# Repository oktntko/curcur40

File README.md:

# curcur40

**curcur40** は、[Corne Keyboard (crkbd v4)](https://github.com/foostan/crkbd) をベースに、**39キー（論理 40入力）左右分割ロープロファイル配列**、右手親指の **25 mm 光学式トラックボール**、右手人差し指内側の **アンダープレート パッシブ磁気慣性ホイール**、および **ビルトイン 11.8° テンティング（折りたたみスタンド併用で 24° / 34° 切替対応）密閉ケース** を統合したカスタムエルゴノミクスキーボードです。

> 製作・部品調達・発注手順は **[ビルドガイド (`docs/buildguide_jp.md`)](./docs/buildguide_jp.md)**、各部の設計仕様書は **[3. ドキュメントインデックス](#3-ドキュメントインデックス-documentation-index)** を参照してください。

---

## 1. 外部仕様 (External Specifications)

### 1.1 ギャラリー (Gallery)

- **[3D 組み立てアニメーション動画 (`docs/assets/assembly_animation.mp4`, 1080p 60fps)](./docs/assets/assembly_animation.mp4)**

#### 本体外観（上面・底面）

| 上面ビュー | 底面ビュー（密閉底面・折りたたみスタンド収納ポケット） |
| :---: | :---: |
|  |  |

#### ポインティング機構（25mm トラックボール ＆ アンダープレート慣性ホイール）

| 右手ホイール実装外観 | 慣性ホイールモジュール単体 |
| :---: | :---: |
|  |  |

| トラックボールカップ単体 | 25mm ボール・光学系組込 |
| :---: | :---: |
|  |  |

> 機構の動作をブラウザ上で体験できるインタラクティブ図解：
> - **[慣性ホイールの 3つのしくみ (`docs/wheel_mechanism_guide.html`)](./docs/wheel_mechanism_guide.html)**
> - **[キャリングボックスの浅角カムフタ開閉機構 (`docs/carrying_box_lid_guide.html`)](./docs/carrying_box_lid_guide.html)**

#### 基板・トッププレート外観

| 左メイン基板 表面 (`F.Cu`) | 左メイン基板 斜視 | 左メイン基板 裏面 (`B.Cu`) |
| :---: | :---: | :---: |
|  |  |  |

| 右メイン基板 表面 (`F.Cu`) | 右メイン基板 斜視 | 右メイン基板 裏面 (`B.Cu`) |
| :---: | :---: | :---: |
|  |  |  |

| 左トッププレート | 右トッププレート | TBセンサー基板 表 (`F.Cu`) | TBセンサー基板 裏 (`B.Cu`) |
| :---: | :---: | :---: | :---: |
|  |  |  |  |

#### 持ち運び用キャリングボックス（オプション）

| フタ装着時（6面フルカバー収納） | フタ取り外し・スライド挿入時 |
| :---: | :---: |
|  |  |

| ボックス本体 | 差込口断面（ゴム足フローティングレール＆TBキーパー） |
| :---: | :---: |
|  |  |

---

### 1.2 ハードウェア仕様 (Hardware Specifications)

| 項目 | 仕様 |
| :--- | :--- |
| **フォームファクタ** | 左右分割型 カラムスタッガード配列（全キー 1u・ホットスワップ対応） |
| **キー数・入力構成** | **計 40 論理スイッチ入力**（Kailh Choc V2 キースイッチ **39個** ＋ ホイール押し込み静音中クリック **1入力**）<br>・**左手 (21キー)**: メイン `3 × 5` (15) ＋ 人差し指内側縦 2キー ＋ 親指 4キー<br>・**右手 (18キー + 2ポインティング)**: メイン `3 × 5` (15) ＋ 人差し指内側下段 1キー ＋ 親指外側 2キー ＋ **慣性ホイール** ＋ **25 mm トラックボール** |
| **対応キースイッチ / キャップ** | Kailh Choc V2（`CPG1353` シリーズ）専用 ／ ロープロファイル MX 十字ステム 1u キーキャップ（`18.5 × 18.5 mm` 以下） |
| **本体外形寸法（片側）** | 幅 **`118.81 mm`** × 奥行 **`94.40 mm`** × ケース高 **`14.20 mm`（小指外端）〜 `39.02 mm`（親指内端）** |
| **テンティング角度** | ・標準（ケース単体 / スタンド収納時）: **`11.80°`** ビルトインテンティング<br>・底面埋め込み折りたたみスタンド展開時（任意）: **約 `24°`（1段目）／ 約 `34°`（2段目）** |
| **トラックボール（右手親指）** | **直径 `⌀25.0 mm` 光学式**（`800 CPI` / `1000 Hz` ポーリング、3点セラミック球支持、素手着脱可能な 3本爪スナップ保持） |
| **スクロールホイール（右手内側）** | **外径 `⌀22.0 mm × 幅 4.65 mm` 炭素鋼フライホイール**（質量 `13.20 g`、1周 **24ノッチ** 非接触磁気ラチェット［無段階強弱調整可］、長時間慣性フリースピン・指触れ即停止、静音ミドルクリック対応） |
| **接続インターフェース** | ・**PC接続**: 左右どちらでも接続可能な北面 USB Type-C（マスター自動認識）<br>・**左右間接続**: 内側側面 USB Type-C（パッシブ USB 2.0 C-to-C ケーブル使用、PC/充電器誤挿し保護付） |
| **LED ライティング** | 各キー独立 RGB バックライト（計 39灯、QMK RGB Matrix 対応） |
| **キャリングボックス（任意）** | 外寸 **`140.20 × 110.44 × 80.25 mm`**（上下リバーシブル 6面フルカバー直方体、トラックボール・折りたたみスタンド・高さ `≤ 3.0 mm` ゴム足・USB-C マグネット端子を装着したまま収納可能） |

---

### 1.3 ソフトウェア仕様 (Firmware & Keymap Specifications)

#### 基本仕様・特殊キー動作

- **対応ファームウェア**: QMK Firmware / VIA / **Vial（推奨・最大 6レイヤー、GUI リアルタイム編集対応）**
- **ポインティング ＆ スクロール専用カスタムキーコード**（Vial / VIA の `User` / `Custom` タブから任意キーへ配置可能）:

| キーコード (Vial表示) | 機能 |
| :--- | :--- |
| **`SCRL_MO` (`USER00`)** | 押している間、トラックボールが **2D 慣性高速ドラッグスクロール** に切り替わる（離すと即座にブレーキがかかり通常カーソル移動へ復帰） |
| **`SCRL_TG` (`USER01`)** | トラックボールの **2D 慣性高速ドラッグスクロール** をトグル切り替え |
| **`SCRL_SL` (`USER02`)** | 押している間、慣性を無効化した **低速精密 2D ドラッグスクロール** に切り替わる |
| **`WHL_HRZ` (`USER03`)** | 押している間、慣性ホイールの回転出力を **水平スクロール（横スクロール）** に切り替える（※`Shift` キー併用時は OS 標準の `Shift + 縦スクロール` として動作） |

- **ポインティング補助挙動**:
  - **Layer 3 自動スクロール連動**: デフォルトで **Layer 3 が有効な間も自動的に 2D 慣性ドラッグスクロールモード** になります。
  - **タッチ即停止 ＆ ズーム誤爆ガード**: 2D 慣性スクロールの惰走中にトラックボールへ軽く触れるかマウスクリックすると即座に停止します。また惰走中に `Ctrl` / `Alt` / `GUI` を押した場合も自動で慣性を停止し、意図しないブラウザ拡大縮小を防ぎます。
  - **ホイールクリック時ブランキング**: ホイール押し込み（中クリック）前後 `25 ms` の微小角度揺れをマスクし、クリックと同時の誤スクロールを抑止します。
- **ケース解体不要のブートローダ起動（DFU / `RPI-RP2` マウント）**:
  - **Bootmagic**: USB を抜いた状態で、**左手は左上端キー（`Tab` 位置 `[0, 1]`）、右手は右上端キー（`Q` 位置 `[4, 1]`）を押したまま USB を接続**。
  - キーマップ上の `QK_BOOT` キー押下でも即座に書き込みモードへ移行可能。

#### デフォルトキーマップ（Vial 標準構成：全 4レイヤー定義済）

Eucalyn 系をベースにした 40入力レイアウトに、右手内側のマウスクリック（上段＝ホイール押し込み `BTN3`、下段キー＝`BTN1`）と Tap-Hold（`Permissive Hold` ＋ `Hold On Other Key Press` 有効）を組み合わせています。

- **Layer 0（ベースレイヤー）**

| 行 | 左手 1 | 左手 2 | 左手 3 | 左手 4 | 左手 5 | 左手 内側 | 右手 内側 | 右手 5 | 右手 4 | 右手 3 | 右手 2 | 右手 1 |
| :-: | :---: | :---: | :---: | :---: | :---: | :---: | :---: | :---: | :---: | :---: | :---: | :---: |
| **上段** | `Tab` | `W` | `E` | `R` | `F` | `-` | **`BTN3` (Wheel押込)** | `J` | `U` | `I` | `O` | `Q` |
| **中段** | `A` | `S` | `D` | `T` | `G` | `Shift+;` | **`BTN1`** | `H` | `Y` | `K` | `L` | `P` |
| **下段** | `LShift` | `Z` | `X` | `C` | `V` | *(なし)* | *(TB領域)* | `B` | `N` | `M` | `,` | `.` |
| **親指** | | | `LGUI` | `Alt / 無変換` | `Ctrl / Esc` | **`LT(1, Space)`** | *(TB領域)* | *(なし)* | **`LT(2, Enter)`** | **`LT(3, 変換)`** | | |

- **Layer 1（ファンクション・括弧・ナビゲーション：`LT(1, Space)` ホールド）**
  - 左手: 上段 `F2`, `F4`, `F12`, `F11` ／ 中段 `[` (JIS `@`), `Del`, `Enter`, `Bksp`, `Macro 0` (`Win+Alt+Space`) ／ 下段・親指 `Alt + ←/↑/→/↓`
  - 右手: 各種括弧・記号類（`&`, `(`, `)`, `-`, `\`, `~`, `]`, `}`, `_`, `$`, `<`, `>`, `+`）
- **Layer 2（カーソル矢印・編集記号：`LT(2, Enter)` ホールド）**
  - 右手: 矢印キー（`I/J/K/L` 周辺に `↑` / `←` `↓` `→`）および `Bksp`, `Del`, 引用符・イコール・セミコロン類
- **Layer 3（テンキー・PageUp/Down ＋ トラックボール 2D慣性スクロール自動有効：`LT(3, 変換)` ホールド）**
  - 左手: `PageUp` / `Home`, `PageDown`, `End`、`#`
  - 右手: 3×3 テンキー（`0`〜`9`）および四則演算記号
- **Vial 初期プリセット（GUI から自由に変更・無効化可能）**:
  - **コンボ**: `BTN1` ＋ `H` 同時押し → **`BTN2`（右クリック）**
  - **Key Overrides（11種）**: JIS 環境向けのシフト記号リマップや修飾キー組み合わせ補正をプリセット収録。

---

## 2. ライセンス・謝辞 (License & Credits)

本プロジェクトは以下のオープンソースプロジェクトをベースに派生・設計されています。各オリジナル作者の皆様に深く感謝いたします。

| 対象領域 | 派生元・原著作者 | 適用ライセンス | 改変時期・主な改変内容（CC BY 4.0 Sec. 3(a) / CERN-OHL-P v2 Sec. 3.3 準拠） |
| :--- | :--- | :--- | :--- |
| **基板・プレート・ケース・ホイール・ドキュメント・スクリプト**<br>(`pcbs/`, `plates/`, `cases/`, `docs/`, `scripts/`) | **[foostan/crkbd](https://github.com/foostan/crkbd)**<br>(`foostan` / Kosuke Adachi) | **[MIT License](./LICENSE_MIT)** ＆<br>**[CC BY 4.0](./LICENSE_CC)** | `2026-10`〜`2026-11`: Corne v4 をベースに 39キー＋中クリック配列化、右手 25mm トラックボール（低プロファイル分離サブ基板）＆アンダープレート パッシブ磁気慣性ホイール（`45# Steel` ローター＋オンボード `TMAG5273`）統合、KiCad 10.0 対応、ヒートセット密閉テンティングケース・キャリングボックス新規設計 |
| **KiCad カスタムライブラリ**<br>(`pcbs/common/kbd/` 内 `kbd.*`) | **[foostan/kbd](https://github.com/foostan/kbd)**<br>(`foostan`) | **[MIT License](./pcbs/common/kbd/LICENSE)** | `2026-10`: 未使用定義の整理、KiCad 10.0 標準シンボル整合、`YS-SK6812MINI-E` Pin 2 (`DOUT`) 電気属性修正、`Kailh_Square_Silent_6.2x6.2mm` 追加、相対 3Dモデルパス化 |
| **PMW3360 シンボル・フットプリント**<br>(`pmw3360_pcb.kicad_sym`, `PMW3360DM-T2QU_16Pin.kicad_mod`) | **[siderakb/pmw3360-pcb](https://github.com/siderakb/pmw3360-pcb)**<br>(`siderakb` / `ziteh`) | **[CERN-OHL-P v2](./LICENSE_CERN_OHL_P_V2)** | `2026-10`: 未使用の `TXS0108E-QPWRQ1` シンボル削除、`PMW3360DM-T2QU` Pin 3 (`VDDPIX`) を `power_out` へ修正、KiCad 10.0 スルーホールパッド層補完、専用サブ基板 `curcur40-pmw3360` へ統合 |
| **ファームウェア (`kbd_firmware/`)**<br>(`kbd_firmware/keyboards/curcur40/`) | **[foostan/kbd_firmware](https://github.com/foostan/kbd_firmware)**<br>**[QMK](https://github.com/qmk/qmk_firmware)** / **[Vial-QMK](https://github.com/vial-kb/vial-qmk)** | **GPL-2.0-or-later** | `2026-10`〜`2026-11`: 40入力マトリクス、`I2C0` `TMAG5273`/`TLV493D-A1B6` 3Dホール慣性ホイール駆動 ＆ `SPI1` `PMW3360` 2D慣性ドラッグスクロール複合ポインティングドライバへ改変 |

---

## 3. ドキュメントインデックス (Documentation Index)

| ドキュメント | 対象読者・内容 |
| :--- | :--- |
| **[ビルドガイド (`docs/buildguide_jp.md`)](./docs/buildguide_jp.md)** | **製作・発注する方向け**: 購入パーツ一覧（BOM・URL）、JLCPCB / JLC3DP / JLCCNC の実発注手順とノウハウ、熱圧入・組立・FW書き込み手順 |
| **[ケース・プレート設計仕様書 (`docs/case_spec.md`)](./docs/case_spec.md)** | **内部設計**: 垂直 Z軸スタックアップ、全 19箇所インサート座標、トッププレート、ボトムケース・スタンドポケット・USB-C 受け棚の設計根拠 |
| **[PCB・回路設計仕様書 (`docs/pcb_spec.md`)](./docs/pcb_spec.md)** | **内部設計**: 全3基板＋3-in-1 パネル仕様、電源/ESD/左右判定/センサー回路の設計根拠、RP2040 ピンアサイン、SMD 部品（LCSC）一覧 |
| **[トラックボール設計仕様書 (`docs/trackball_spec.md`)](./docs/trackball_spec.md)** | **内部設計**: PMW3360 + LM19 光学距離（`2.40 mm`）設計、55° セラミック支持球の乗り上げ防止力学、2D慣性ドラッグスクロール FW 処理 |
| **[慣性ホイール設計仕様書 (`docs/wheel_spec.md`)](./docs/wheel_spec.md)** | **内部設計**: `⌀2.00 H7` 中心貫通穴 `45# Steel` フライホイール、平行ピン＆シム内輪支持、Cクリップシーソー機構、無段階磁気デテント、オンボード 3Dホール角度復調 FW 処理 |
| **[キャリングボックス設計仕様書 (`docs/carrying_box_spec.md`)](./docs/carrying_box_spec.md)** | **内部設計**: 互い違いウェッジ相殺配置、ゴム足フローティングレール、長スパン浅角カム式スナップフタの力学設計 |
| **[体験型 HTML 図解: 慣性ホイール (`docs/wheel_mechanism_guide.html`)](./docs/wheel_mechanism_guide.html)** | ブラウザで動かせる慣性スピン・磁気ノッチ調整・シーソークリックのインタラクティブ解説 |
| **[体験型 HTML 図解: スナップフタ (`docs/carrying_box_lid_guide.html`)](./docs/carrying_box_lid_guide.html)** | ブラウザで動かせるキャリングボックス浅角カムスナップフタの開閉力学解説 |
| **[スクリプト・自動検証リファレンス (`scripts/README.md`)](./scripts/README.md)** | **開発・検証向け**: 3D CAD・プレート・JLCPCB データ・プレビュー生成スクリプト（全 12本）の実行方法と DFM / 6-DOF / 干渉ゼロ検証基準 |
| **[ファームウェア README (`kbd_firmware/readme.md`)](./kbd_firmware/readme.md)** | QMK / Vial ビルドコマンドおよびカスタムキーコード概要（英語） |

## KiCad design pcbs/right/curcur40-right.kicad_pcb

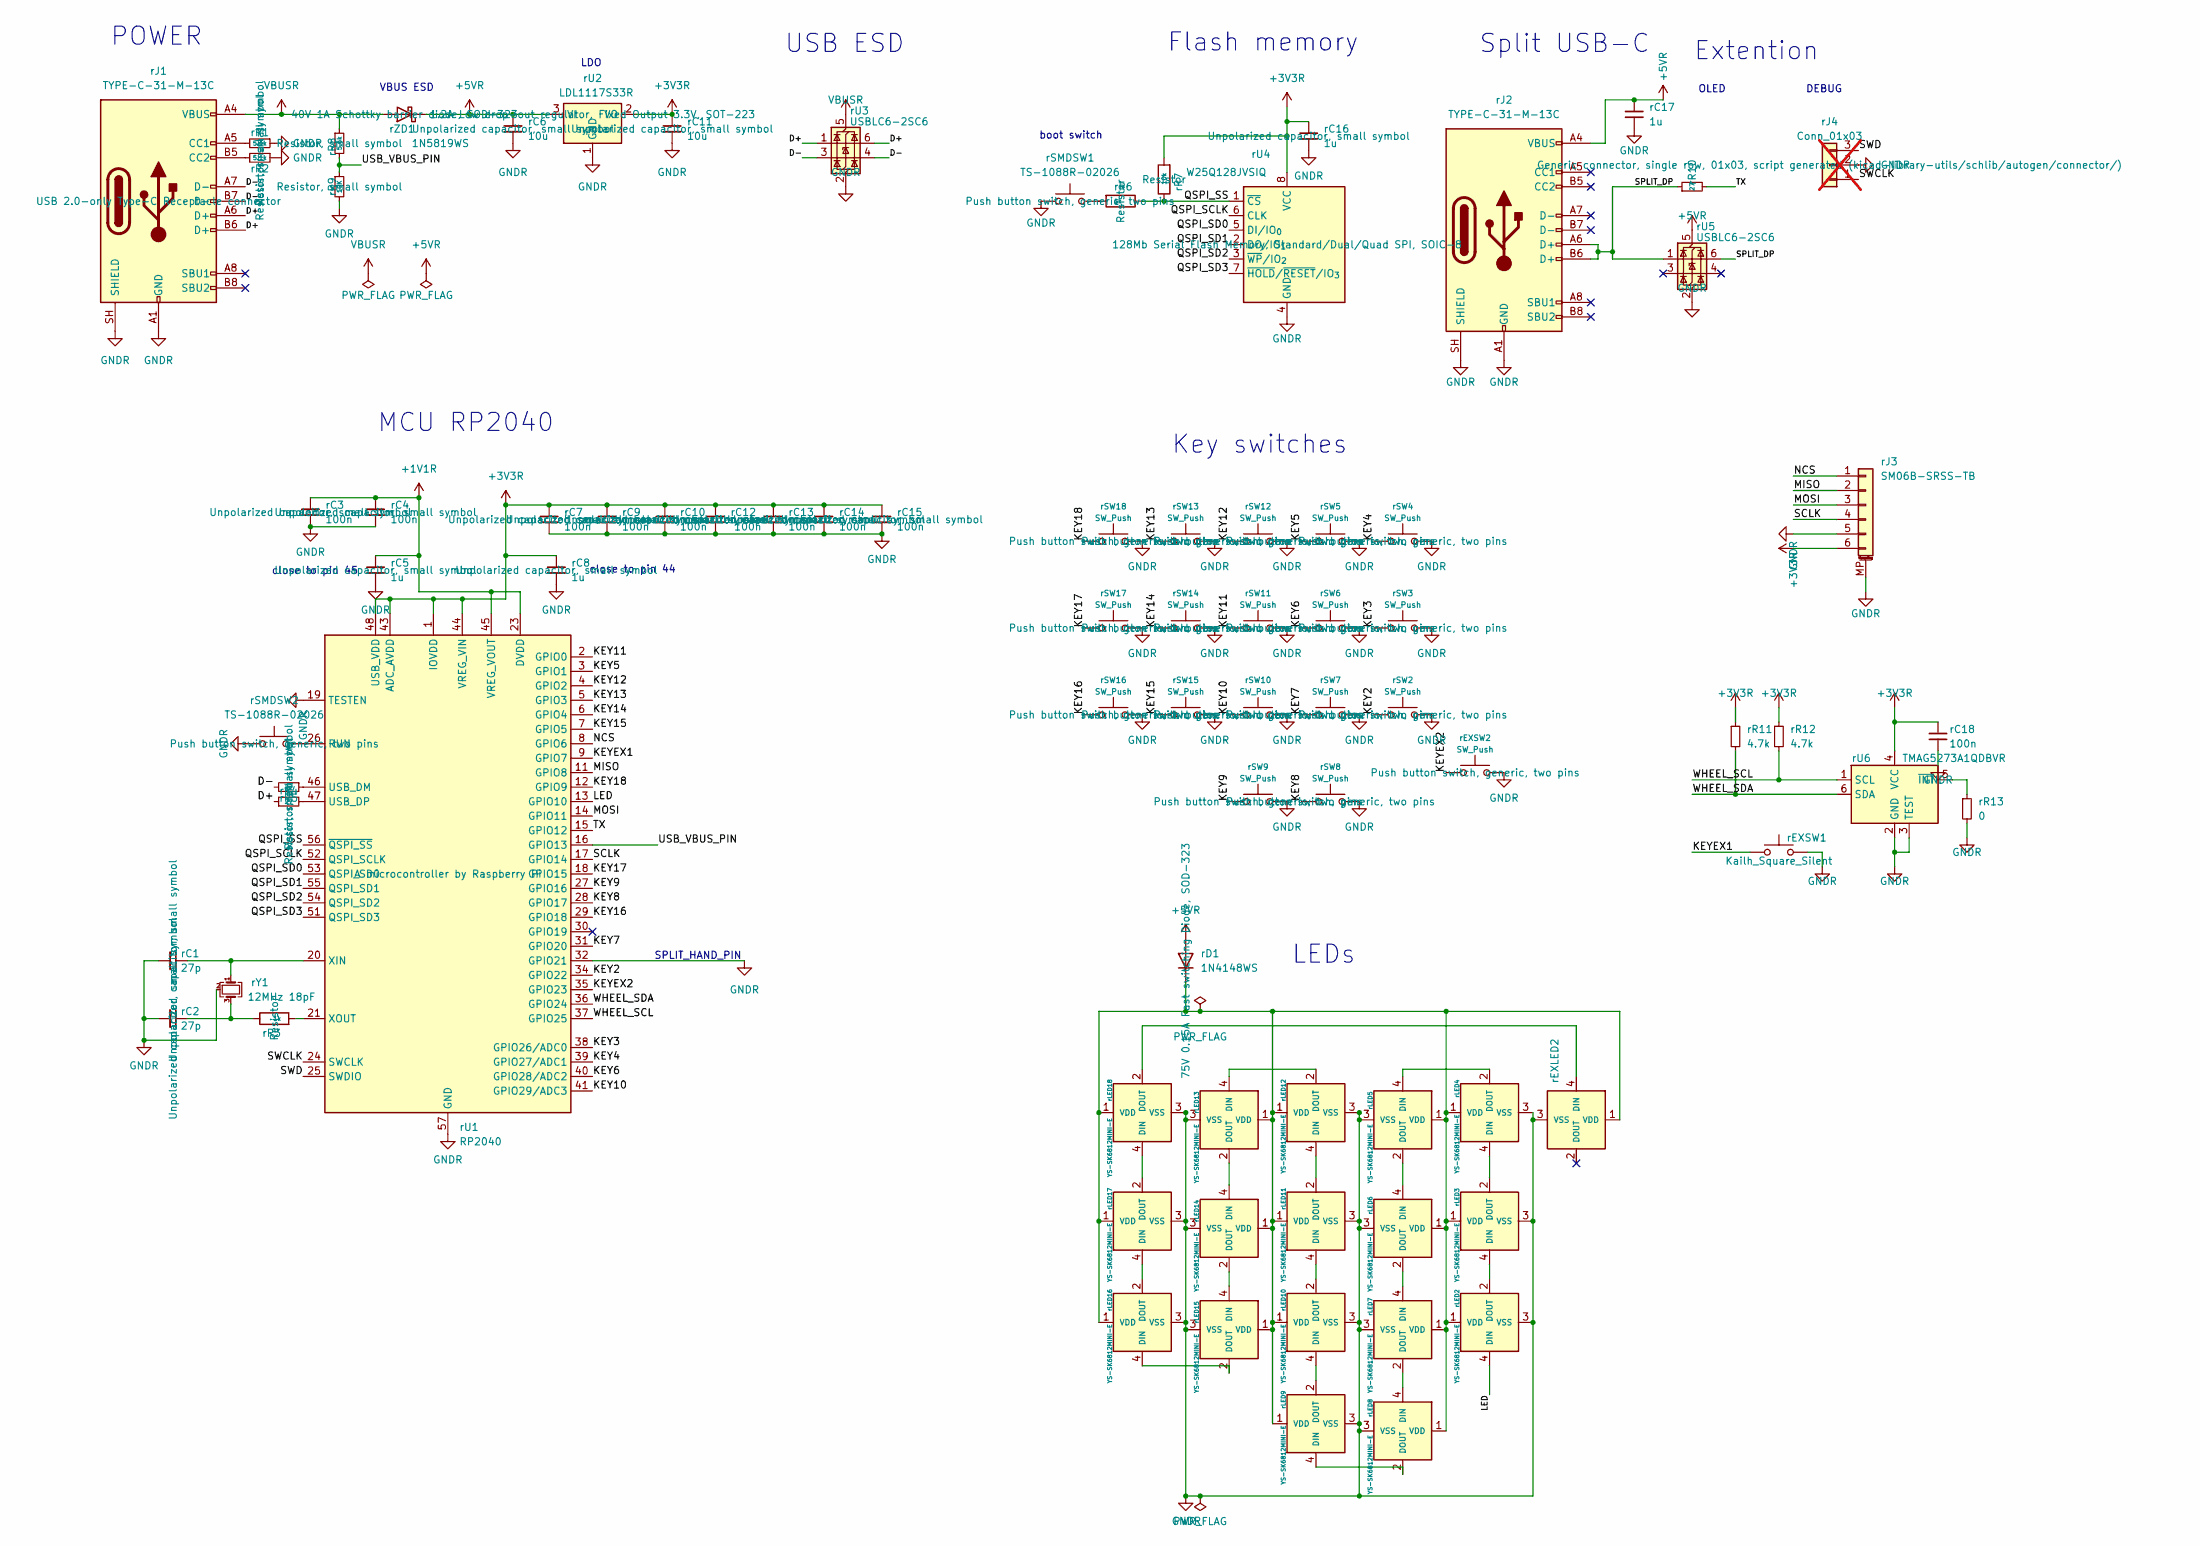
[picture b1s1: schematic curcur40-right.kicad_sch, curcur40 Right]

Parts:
rC1, rC2: 27p; C_0402_1005Metric
rC3, rC4, rC7, rC9, rC10, rC12, rC13, rC14, rC15: 100n; C_0402_1005Metric
rC5, rC8, rC16: 1u; C_0402_1005Metric
rC6, rC11: 10u; C_0402_1005Metric
rC17: 1u; C_0402_1005Metric; JLCPCB Part # C52923
rC18: 100n; C_0402_1005Metric; JLCPCB Part # C1525
rD1: 1N4148WS; D_SOD-323; JLCPCB Part # C2128
rEXLED2: YS-SK6812MINI-E
rEXSW1: Kailh_Square_Silent; Kailh_Square_Silent_6.2x6.2mm
rEXSW2: SW_Push; keyswitch_choc12_hotswap_1u
rJ1, rJ2: TYPE-C-31-M-13C; USB_C_Receptacle_TYPE-C-31-M-13C; JLCPCB Part # C2848620
rJ3: SM06B-SRSS-TB; JST_SH_SM06B-SRSS-TB_1x06-1MP_P1.00mm_Horizontal; LCSC C160405
rJ4: Conn_01x03; PinHeader_1x03_P2.54mm_Vertical; not fitted
rLED2, rLED3, rLED4, rLED5, rLED6, rLED7, rLED8, rLED9, rLED10, rLED11, rLED12, rLED13, rLED14, rLED15, rLED16, rLED17, rLED18: YS-SK6812MINI-E
rR1, rR2: 5.1k; R_0402_1005Metric
rR3, rR6: 1k; R_0402_1005Metric
rR4, rR5: 27; R_0402_1005Metric
rR7: 10k; R_0402_1005Metric
rR8: 5.6k; R_0402_1005Metric
rR9: 10K; R_0402_1005Metric
rR10: 27; R_0402_1005Metric; JLCPCB Part # C2909343
rR11, rR12: 4.7k; R_0402_1005Metric
rR13: 0; R_0402_1005Metric; LCSC C17168
rSMDSW1, rSMDSW2: TS-1088R-02026; JLCPCB Part # C455280
rSW2, rSW3, rSW4, rSW5, rSW6, rSW7, rSW8, rSW9, rSW10, rSW11, rSW12, rSW13, rSW14, rSW15, rSW16, rSW17, rSW18: SW_Push; keyswitch_choc12_hotswap_1u
rU1: RP2040; QFN-56-1EP_7x7mm_P0.4mm_EP3.2x3.2mm; JLCPCB Part # C2040
rU2: LDL1117S33R; SOT-223-3_TabPin2; JLCPCB Part # C435835
rU3, rU5: USBLC6-2SC6; SOT-23-6; JLCPCB Part # C7519
rU4: W25Q128JVSIQ; SOIC-8_5.3x5.3mm_P1.27mm; JLCPCB Part # C113767
rU6: TMAG5273A1QDBVR; SOT-23-6; LCSC C3716049
rY1: 12MHz 18pF; Crystal_SMD_3225-4Pin_3.2x2.5mm; MFR.Part # Q22FA23V0041800; JLCPCB Part # C91749
rZD1: 1N5819WS; D_SOD-323; JLCPCB Part # C191023

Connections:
+1V1R: rC3.1, rC4.1, rC5.1, rU1.23 (DVDD), rU1.45 (VREG_VOUT), rU1.50 (DVDD)
+3V3R: rC7.1, rC8.1, rC9.1, rC10.1, rC11.1, rC12.1, rC13.1, rC14.1, rC15.1, rC16.1, rC18.1, rJ3.6, rR7.2, rR11.1, rR12.1, rU1.1 (IOVDD), rU1.10 (IOVDD), rU1.22 (IOVDD), rU1.33 (IOVDD), rU1.42 (IOVDD), rU1.43 (ADC_AVDD), rU1.44 (VREG_VIN), rU1.48 (USB_VDD), rU1.49 (IOVDD), rU2.2 (VO), rU4.8 (VCC), rU6.4 (VCC)
+5VR: rC6.1, rC17.1, rD1.2 (A), rJ2.A4 (VBUS), rJ2.A9 (VBUS), rJ2.B4 (VBUS), rJ2.B9 (VBUS), rU2.3 (VI), rU5.5 (VBUS), rZD1.1 (K)
/D+: rJ1.A6 (D+), rJ1.B6 (D+), rR4.1, rU3.1 (I/O1), rU3.6 (I/O1)
/D-: rJ1.A7 (D-), rJ1.B7 (D-), rR5.2, rU3.3 (I/O2), rU3.4 (I/O2)
/KEY2: rSW2.1, rU1.34 (GPIO22)
/KEY3: rSW3.1, rU1.38 (GPIO26/ADC0)
/KEY4: rSW4.1, rU1.39 (GPIO27/ADC1)
/KEY5: rSW5.1, rU1.3 (GPIO1)
/KEY6: rSW6.1, rU1.40 (GPIO28/ADC2)
/KEY7: rSW7.1, rU1.31 (GPIO20)
/KEY8: rSW8.1, rU1.28 (GPIO17)
/KEY9: rSW9.1, rU1.27 (GPIO16)
/KEY10: rSW10.1, rU1.41 (GPIO29/ADC3)
/KEY11: rSW11.1, rU1.2 (GPIO0)
/KEY12: rSW12.1, rU1.4 (GPIO2)
/KEY13: rSW13.1, rU1.5 (GPIO3)
/KEY14: rSW14.1, rU1.6 (GPIO4)
/KEY15: rSW15.1, rU1.7 (GPIO5)
/KEY16: rSW16.1, rU1.29 (GPIO18)
/KEY17: rSW17.1, rU1.18 (GPIO15)
/KEY18: rSW18.1, rU1.12 (GPIO9)
/KEYEX1: rEXSW1.1, rU1.9 (GPIO7)
/KEYEX2: rEXSW2.1, rU1.35 (GPIO23)
/LED: rLED2.4 (DIN), rU1.13 (GPIO10)
/MISO: rJ3.2, rU1.11 (GPIO8)
/MOSI: rJ3.3, rU1.14 (GPIO11)
/NCS: rJ3.1, rU1.8 (GPIO6)
/QSPI_SCLK: rU1.52 (QSPI_SCLK), rU4.6 (CLK)
/QSPI_SD0: rU1.53 (QSPI_SD0), rU4.5 (DI/IO_{0})
/QSPI_SD1: rU1.55 (QSPI_SD1), rU4.2 (DO/IO_{1})
/QSPI_SD2: rU1.54 (QSPI_SD2), rU4.3 (~WP/IO_{2})
/QSPI_SD3: rU1.51 (QSPI_SD3), rU4.7 (~HOLD/~RESET/IO_{3})
/QSPI_SS: rR6.1, rR7.1, rU1.56 (~QSPI_SS), rU4.1 (~CS)
/SCLK: rJ3.4, rU1.17 (GPIO14)
/SPLIT_DP: rJ2.A6 (D+), rJ2.B6 (D+), rR10.1, rU5.1 (I/O1), rU5.6 (I/O1)
/SWCLK: rJ4.1, rU1.24 (SWCLK)
/SWD: rJ4.3, rU1.25 (SWDIO)
/TX: rR10.2, rU1.15 (GPIO12)
/USB_VBUS_PIN: rR8.2, rR9.1, rU1.16 (GPIO13)
/WHEEL_SCL: rR12.2, rU1.37 (GPIO25), rU6.1 (SCL)
/WHEEL_SDA: rR11.2, rU1.36 (GPIO24), rU6.6 (SDA)
GNDR: rC1.2, rC2.2, rC3.2, rC4.2, rC5.2, rC6.2, rC7.2, rC8.2, rC9.2, rC10.2, rC11.2, rC12.2, rC13.2, rC14.2, rC15.2, rC16.2, rC17.2, rC18.2, rEXLED2.3 (VSS), rEXSW1.2, rEXSW2.2, rJ1.A1 (GND), rJ1.A12 (GND), rJ1.B1 (GND), rJ1.B12 (GND), rJ1.SH (SHIELD), rJ2.A1 (GND), rJ2.A12 (GND), rJ2.B1 (GND), rJ2.B12 (GND), rJ2.SH (SHIELD), rJ3.5, rJ3.MP (MountPin), rJ4.2, rLED2.3 (VSS), rLED3.3 (VSS), rLED4.3 (VSS), rLED5.3 (VSS), rLED6.3 (VSS), rLED7.3 (VSS), rLED8.3 (VSS), rLED9.3 (VSS), rLED10.3 (VSS), rLED11.3 (VSS), rLED12.3 (VSS), rLED13.3 (VSS), rLED14.3 (VSS), rLED15.3 (VSS), rLED16.3 (VSS), rLED17.3 (VSS), rLED18.3 (VSS), rR1.1, rR2.1, rR9.2, rR13.2, rSMDSW1.1, rSMDSW2.1, rSW2.2, rSW3.2, rSW4.2, rSW5.2, rSW6.2, rSW7.2, rSW8.2, rSW9.2, rSW10.2, rSW11.2, rSW12.2, rSW13.2, rSW14.2, rSW15.2, rSW16.2, rSW17.2, rSW18.2, rU1.19 (TESTEN), rU1.32 (GPIO21), rU1.57 (GND), rU2.1 (GND), rU3.2 (GND), rU4.4 (GND), rU5.2 (GND), rU6.2 (GND), rU6.3 (TEST), rY1.2 (G), rY1.4 (G)
unnamed: rC2.1, rR3.1, rY1.3
unnamed: rD1.1 (K), rEXLED2.1 (VDD), rLED2.1 (VDD), rLED3.1 (VDD), rLED4.1 (VDD), rLED5.1 (VDD), rLED6.1 (VDD), rLED7.1 (VDD), rLED8.1 (VDD), rLED9.1 (VDD), rLED10.1 (VDD), rLED11.1 (VDD), rLED12.1 (VDD), rLED13.1 (VDD), rLED14.1 (VDD), rLED15.1 (VDD), rLED16.1 (VDD), rLED17.1 (VDD), rLED18.1 (VDD)
unnamed: rEXLED2.4 (DIN), rLED18.2 (DOUT)
unnamed: rJ1.A5 (CC1), rR1.2
unnamed: rJ1.B5 (CC2), rR2.2
unnamed: rLED2.2 (DOUT), rLED3.4 (DIN)
unnamed: rLED3.2 (DOUT), rLED4.4 (DIN)
unnamed: rLED4.2 (DOUT), rLED5.4 (DIN)
unnamed: rLED5.2 (DOUT), rLED6.4 (DIN)
unnamed: rLED6.2 (DOUT), rLED7.4 (DIN)
unnamed: rLED7.2 (DOUT), rLED8.4 (DIN)
unnamed: rLED8.2 (DOUT), rLED9.4 (DIN)
unnamed: rLED9.2 (DOUT), rLED10.4 (DIN)
unnamed: rLED10.2 (DOUT), rLED11.4 (DIN)
unnamed: rLED11.2 (DOUT), rLED12.4 (DIN)
unnamed: rLED12.2 (DOUT), rLED13.4 (DIN)
unnamed: rLED13.2 (DOUT), rLED14.4 (DIN)
unnamed: rLED14.2 (DOUT), rLED15.4 (DIN)
unnamed: rLED15.2 (DOUT), rLED16.4 (DIN)
unnamed: rLED16.2 (DOUT), rLED17.4 (DIN)
unnamed: rLED17.2 (DOUT), rLED18.4 (DIN)
unnamed: rR6.2, rSMDSW1.2
unnamed: rSMDSW2.2, rU1.26 (RUN)
unnamed: rR5.1, rU1.46 (USB_DM)
unnamed: rR4.2, rU1.47 (USB_DP)
unnamed: rC1.1, rU1.20 (XIN), rY1.1
unnamed: rR3.2, rU1.21 (XOUT)
unnamed: rR13.1, rU6.5 (~INT)
VBUSR: rJ1.A4 (VBUS), rJ1.A9 (VBUS), rJ1.B4 (VBUS), rJ1.B9 (VBUS), rR8.1, rU3.5 (VBUS), rZD1.2 (A)

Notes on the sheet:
USB ESD
Split USB-C
Flash memory
MCU RP2040
DEBUG
POWER
boot switch
LDO
Key switches
LEDs
Extention
VBUS ESD
OLED
close to pin 45
close to pin 44
SPLIT_HAND_PIN

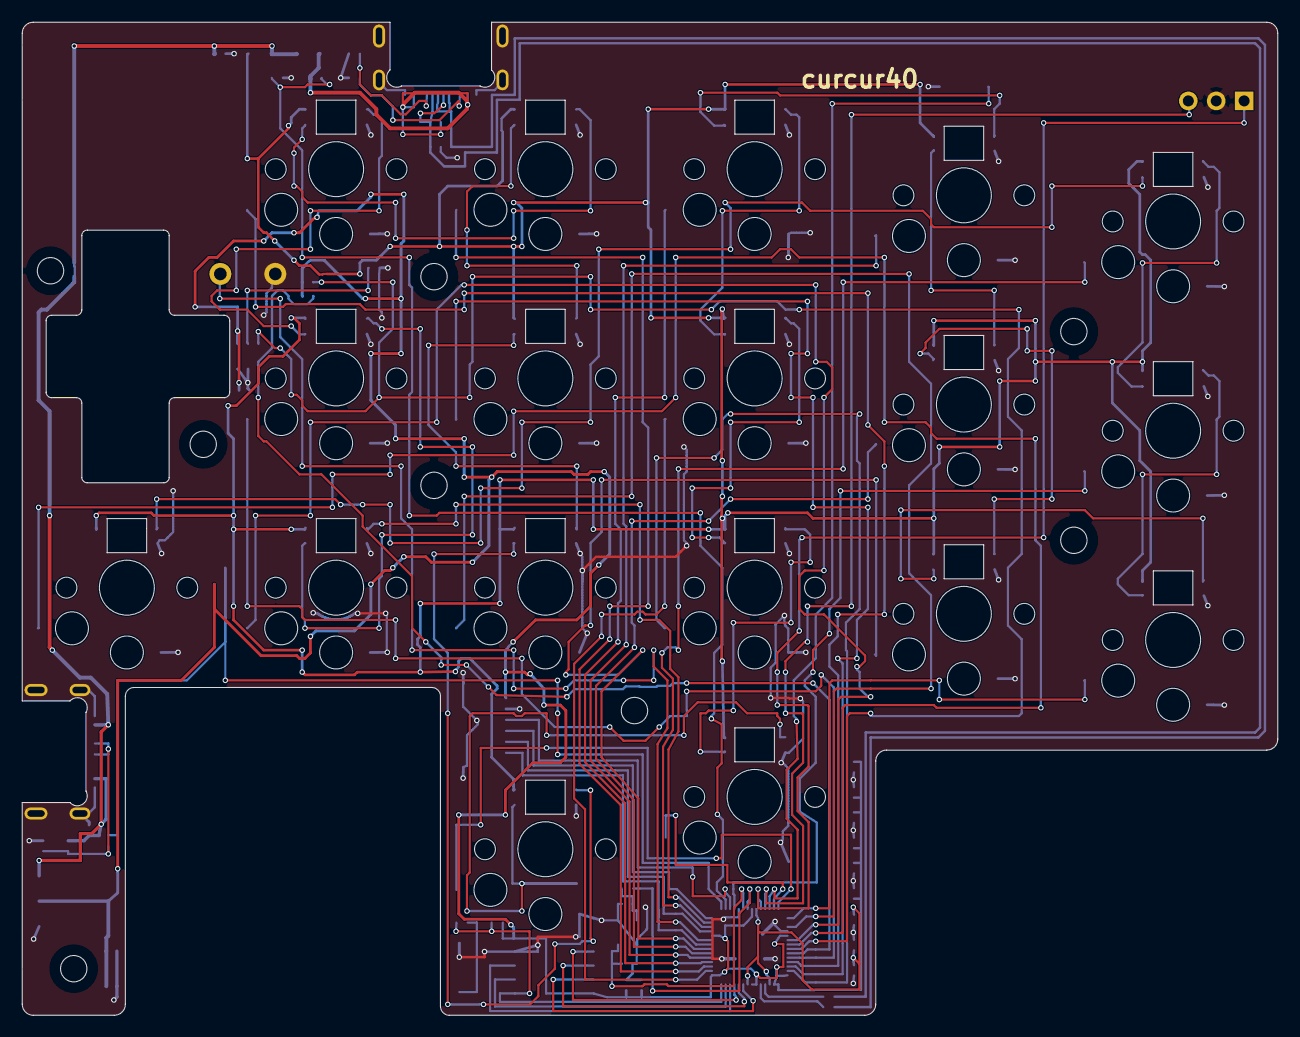
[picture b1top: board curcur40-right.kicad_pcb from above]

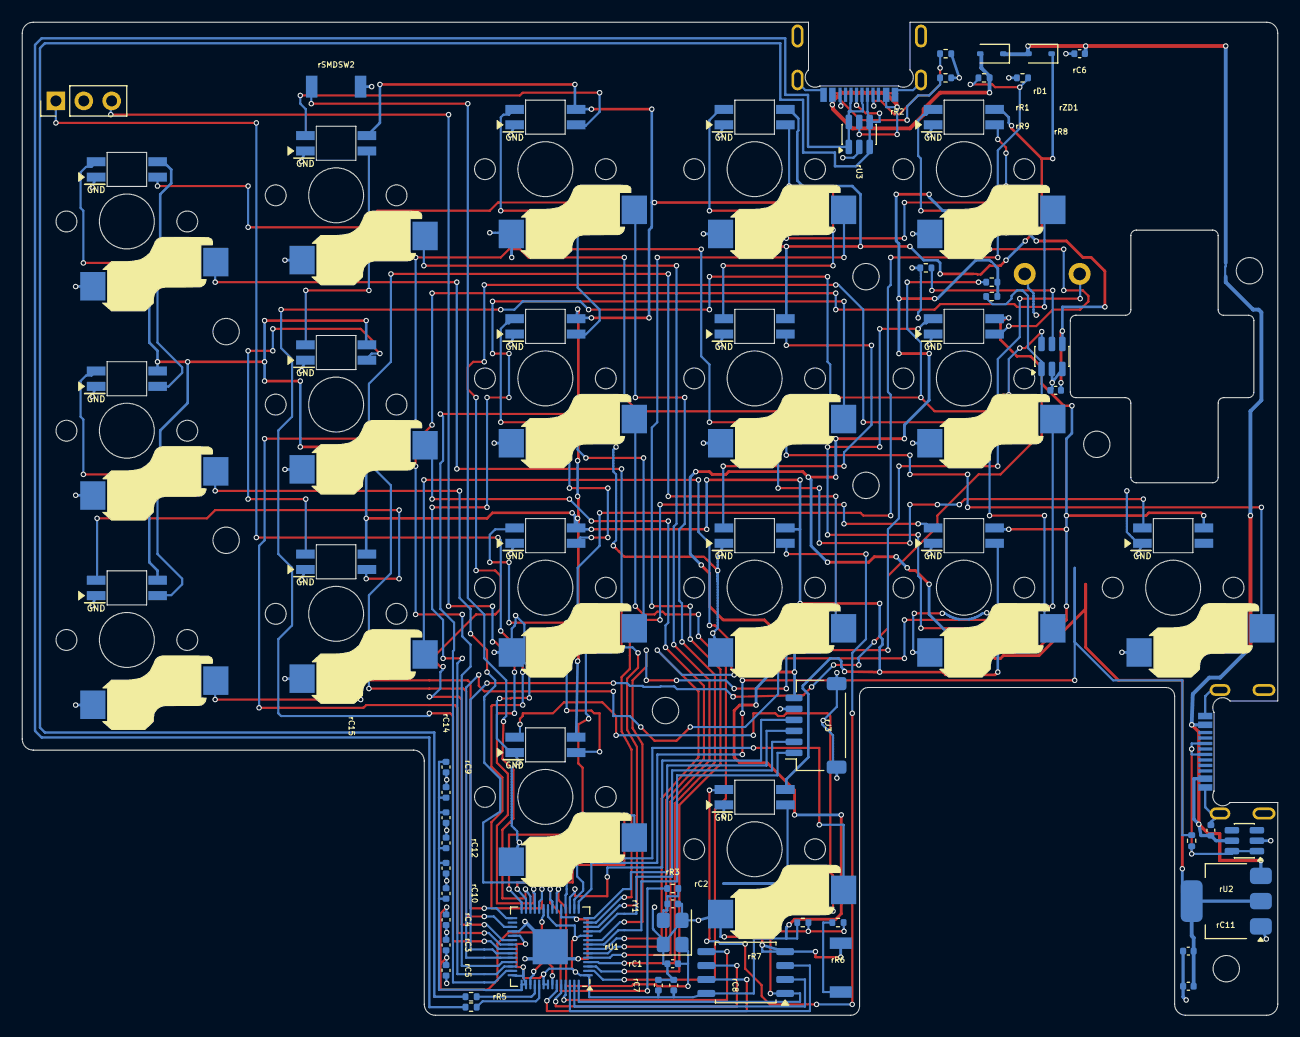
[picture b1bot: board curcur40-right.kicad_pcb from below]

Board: 2 copper layers, 114.3 x 90.4 mm, 83 parts (83 on the bottom side), 72 nets.

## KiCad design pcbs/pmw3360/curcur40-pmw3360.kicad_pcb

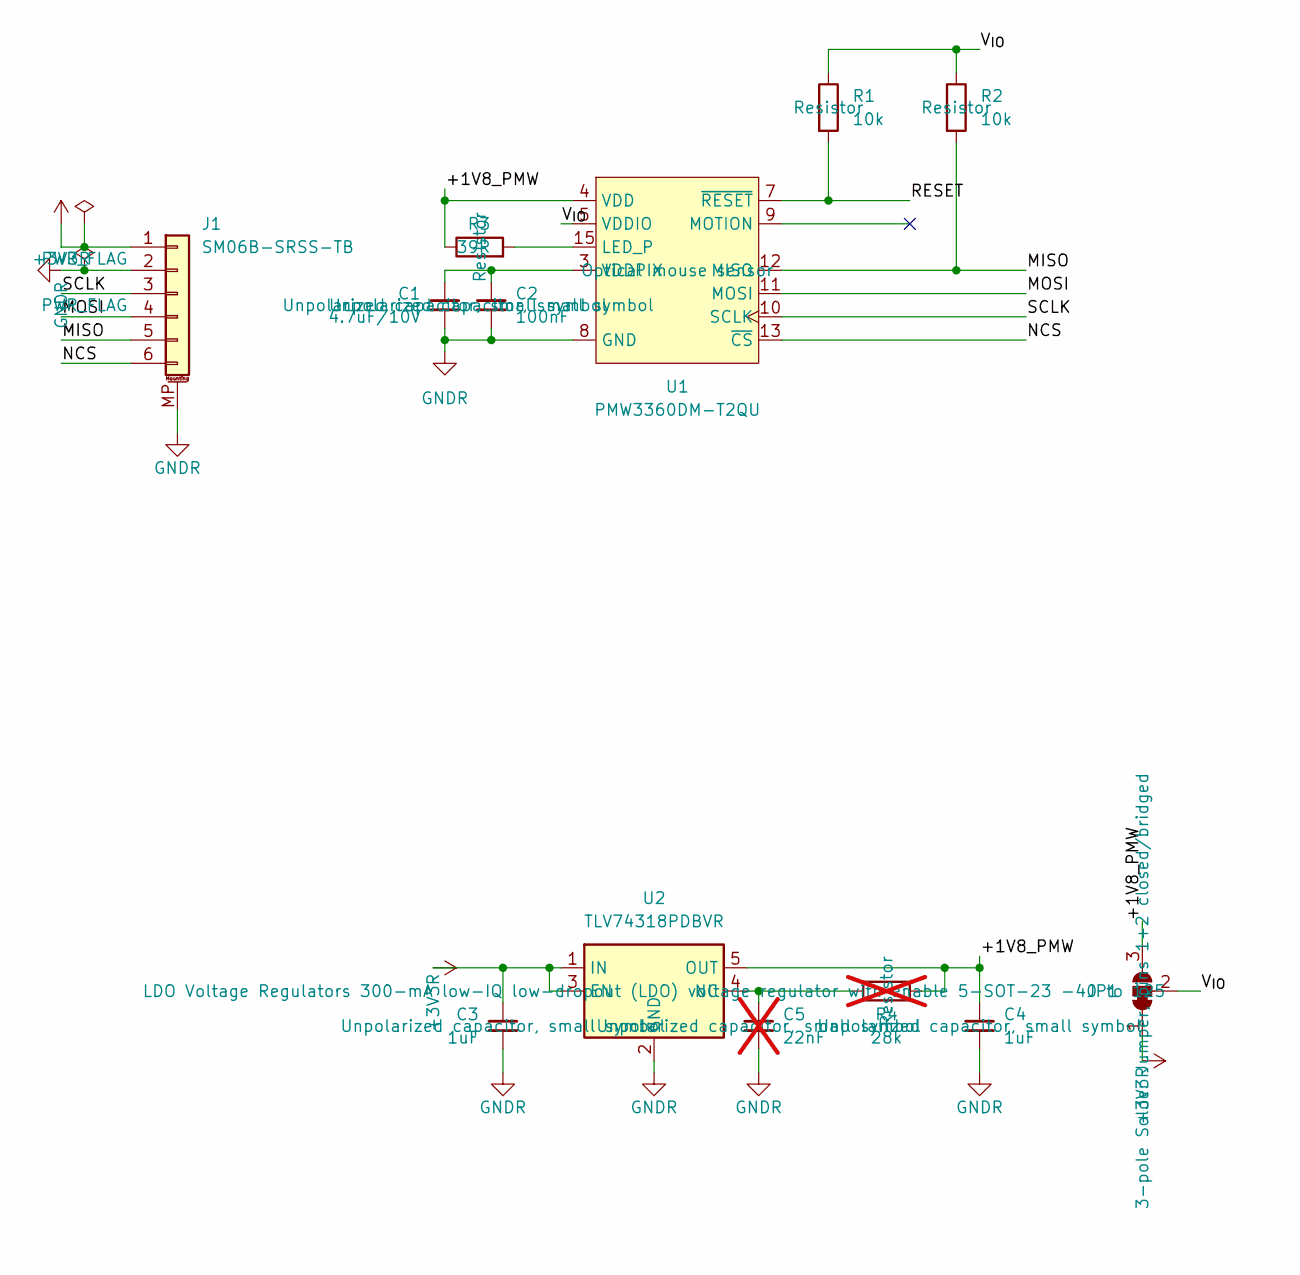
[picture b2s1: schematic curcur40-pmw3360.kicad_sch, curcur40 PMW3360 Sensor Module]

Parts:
C1: 4.7uF/10V; C_0603_1608Metric_Pad1.08x0.95mm_HandSolder; Mfr. # CL10A475KO8NNNC; LCSC C19666
C2: 100nF; C_0603_1608Metric_Pad1.08x0.95mm_HandSolder; Mfr. # CC0603KRX7R9BB104; LCSC C14663
C3, C4: 1uF; C_0603_1608Metric_Pad1.08x0.95mm_HandSolder; Mfr. # CL10A105KB8NNNC; LCSC C15849
C5: 22nF; C_0603_1608Metric_Pad1.08x0.95mm_HandSolder; Mfr. # CL10B223KB8NNNC; LCSC C21122; not fitted
J1: SM06B-SRSS-TB; JST_SH_SM06B-SRSS-TB_1x06-1MP_P1.00mm_Horizontal; LCSC C160405
JP1: SolderJumper_3_Bridged12; SolderJumper-3_P1.3mm_Bridged12_RoundedPad1.0x1.5mm_NumberL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
R1, R2: 10k; R_0603_1608Metric_Pad0.98x0.95mm_HandSolder; Mfr. # 0603WAF1002T5E; LCSC C25804
R3: 39R; R_0603_1608Metric_Pad0.98x0.95mm_HandSolder; Mfr. # 0603WAF390JT5E; LCSC C23154
R4: 28k; R_0603_1608Metric_Pad0.98x0.95mm_HandSolder; not fitted
U1: PMW3360DM-T2QU; PMW3360DM-T2QU_16Pin
U2: TLV74318PDBVR; SOT-23-5; Mfr. # TLV74318PDBVR; LCSC C485152

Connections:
+3V3R: C3.1, J1.1, JP1.1 (A), U2.1 (IN), U2.3 (EN)
/+1V8_PMW: C4.1, JP1.3 (B), R3.1, R4.1, U1.4 (VDD), U2.5 (OUT)
/MISO: J1.5, R2.2, U1.12 (MISO)
/MOSI: J1.4, U1.11 (MOSI)
/NCS: J1.6, U1.13 (~CS)
/RESET: R1.2, U1.7 (~RESET)
/SCLK: J1.3, U1.10 (SCLK)
/V_{IO}: JP1.2 (C), R1.1, R2.1, U1.5 (VDDIO)
GNDR: C1.2, C2.2, C3.2, C4.2, C5.2, J1.2, J1.MP (MountPin), U1.8 (GND), U2.2 (GND)
unnamed: R3.2, U1.15 (LED_P)
unnamed: C1.1, C2.1, U1.3 (VDDPIX)
unnamed: C5.1, R4.2, U2.4 (NC)

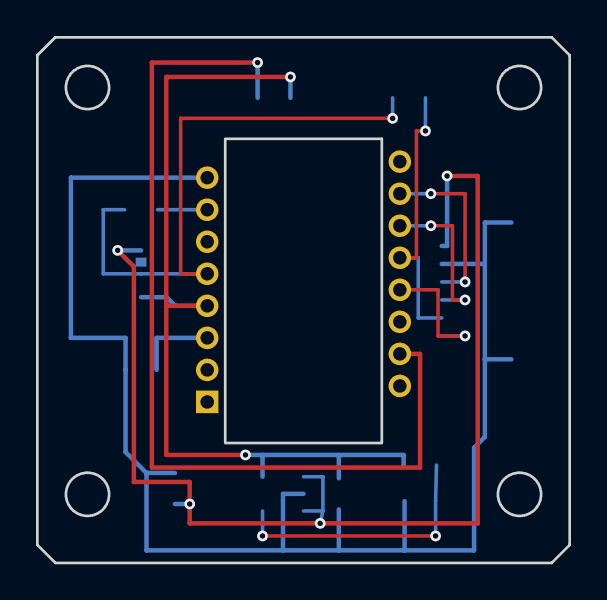
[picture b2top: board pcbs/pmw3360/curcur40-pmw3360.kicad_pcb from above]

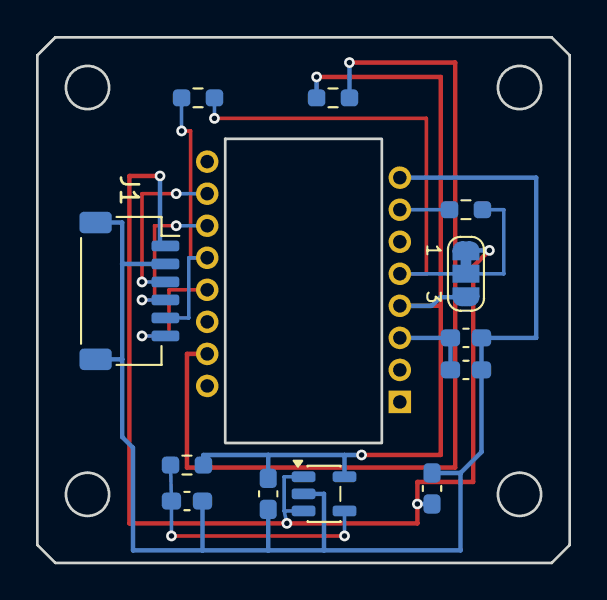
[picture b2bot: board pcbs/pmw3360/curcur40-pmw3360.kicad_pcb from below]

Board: 2 copper layers, 29.6 x 29.2 mm, 13 parts (13 on the bottom side), 12 nets.

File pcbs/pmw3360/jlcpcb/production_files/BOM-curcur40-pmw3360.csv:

Comment,Designator,Footprint,LCSC
100nF,C2,C_0603_1608Metric,C14663
1uF,"C3,C4",C_0603_1608Metric,C15849
SM06B-SRSS-TB(LF)(SN),J1,JST_SH_SM06B-SRSS-TB_1x06-1MP_P1.00mm_Horizontal,C160405
4.7uF/10V,C1,C_0603_1608Metric,C19666
39R,R3,R_0603_1608Metric,C23154
10k,"R1,R2",R_0603_1608Metric,C25804
TLV74318PDBVR,U2,SOT-23-5,C485152

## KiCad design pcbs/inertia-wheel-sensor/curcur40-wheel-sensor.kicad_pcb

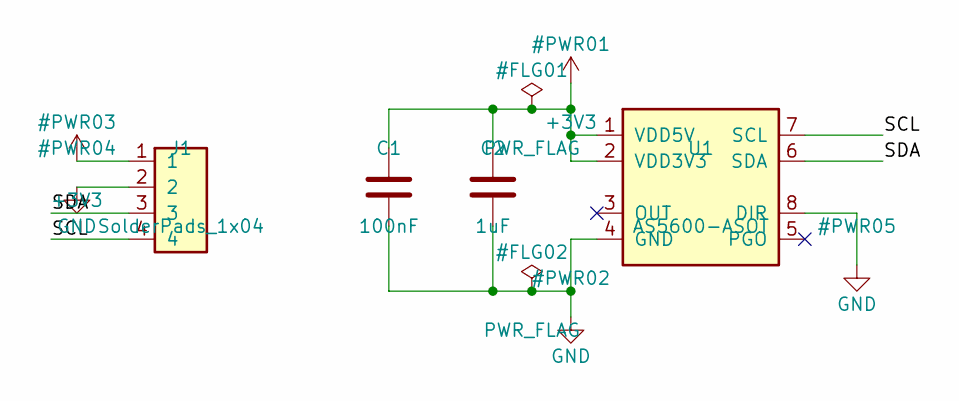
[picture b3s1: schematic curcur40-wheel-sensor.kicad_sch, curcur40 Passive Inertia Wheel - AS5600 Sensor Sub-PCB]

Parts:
C1: 100nF; C_0402_1005Metric; LCSC C1525
C2: 1uF; C_0402_1005Metric; LCSC C52923
J1: SolderPads_1x04; SolderPads_1x04_P1.27mm_SMD
U1: AS5600-ASOT; SOIC-8_3.9x4.9mm_P1.27mm; LCSC C499458

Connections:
+3V3: C1.1, C2.1, J1.1, U1.1 (VDD5V), U1.2 (VDD3V3)
/SCL: J1.4, U1.7 (SCL)
/SDA: J1.3, U1.6 (SDA)
GND: C1.2, C2.2, J1.2, U1.4 (GND), U1.8 (DIR)

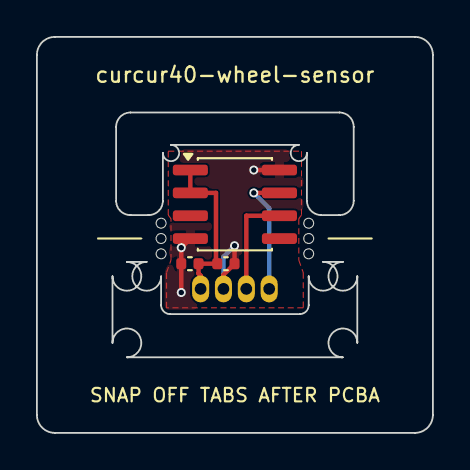
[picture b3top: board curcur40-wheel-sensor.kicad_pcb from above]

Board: 2 copper layers, 22.0 x 22.0 mm, 6 parts (0 on the bottom side), 4 nets.

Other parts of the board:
MB1, MB2: MouseBite; MouseBite_3x0.55mm

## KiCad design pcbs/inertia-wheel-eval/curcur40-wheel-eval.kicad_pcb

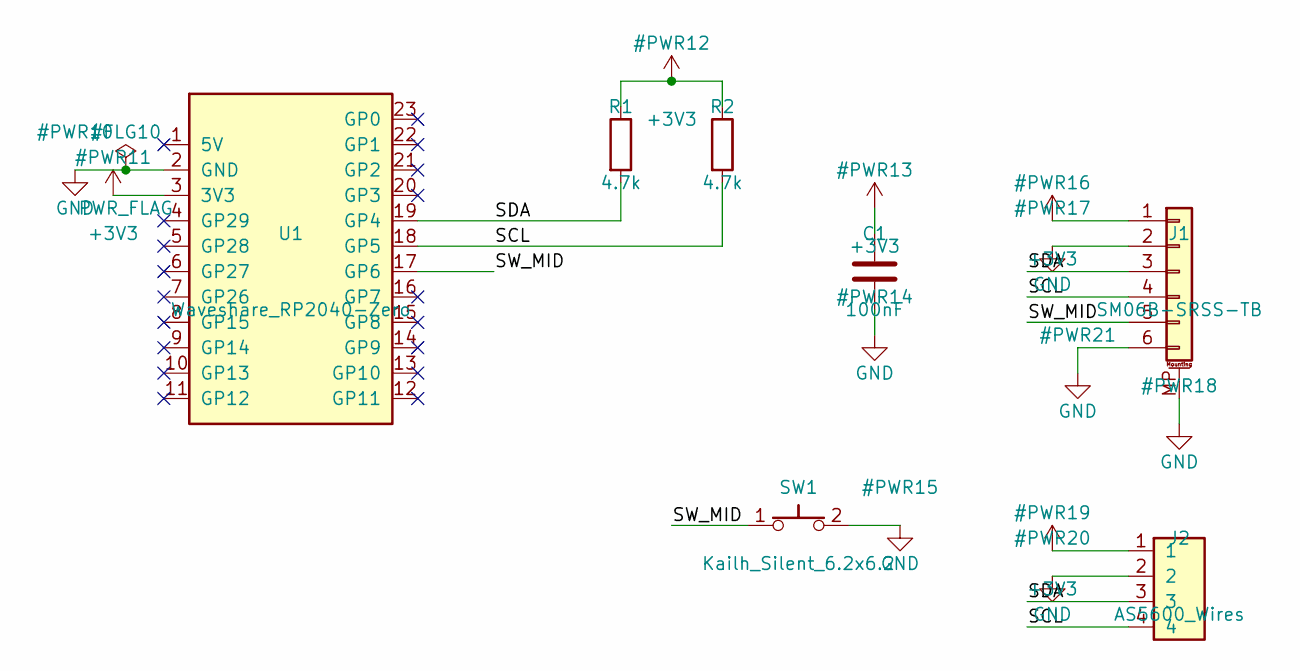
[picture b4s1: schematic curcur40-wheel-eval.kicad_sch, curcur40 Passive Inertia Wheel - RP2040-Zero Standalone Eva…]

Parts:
C1: 100nF; C_0402_1005Metric; LCSC C1525
J1: SM06B-SRSS-TB; JST_SH_SM06B-SRSS-TB_1x06-1MP_P1.00mm_Horizontal; LCSC C160405
J2: AS5600_Wires; SolderPads_1x04_P1.27mm_SMD
R1, R2: 4.7k; R_0402_1005Metric; LCSC C25900
SW1: Kailh_Silent_6.2x6.2; Kailh_Square_Silent_6.2x6.2mm
U1: Waveshare_RP2040-Zero; Waveshare_RP2040-Zero_Castellated

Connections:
+3V3: C1.1, J1.1, J2.1, R1.1, R2.1, U1.3 (3V3)
/SCL: J1.4, J2.4, R2.2, U1.18 (GP5)
/SDA: J1.3, J2.3, R1.2, U1.19 (GP4)
/SW_MID: J1.5, SW1.1, U1.17 (GP6)
GND: C1.2, J1.2, J1.6, J1.MP (MountPin), J2.2, SW1.2, U1.2 (GND)

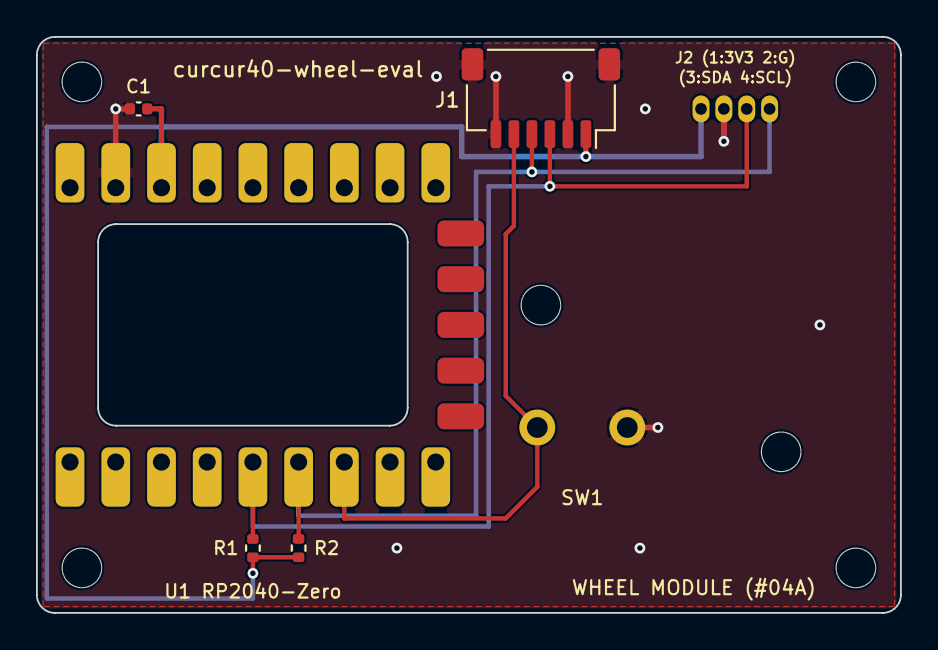
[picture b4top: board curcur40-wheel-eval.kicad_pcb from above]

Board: 2 copper layers, 48.0 x 32.0 mm, 13 parts (0 on the bottom side), 5 nets.

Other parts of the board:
H1, H2, H3, H4, H5, H6: MountingHole; MountingHole_2.2mm_M2

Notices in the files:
pcbs/curcur40/pmw3360/curcur40-pmw3360.kicad_pcb:
Open Source Hardware, CERN-OHL-P v2
